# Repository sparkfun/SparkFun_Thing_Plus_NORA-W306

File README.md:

SparkFun Thing Plus - NORA-W306
========================================

[*SparkFun Thing Plus - NORA-W306 (WRL-21637)*](https://www.sparkfun.com/products/21637)

The SparkFun Thing Plus - NORA-W306 is a Feather form-factor development board equipped with the u-blox NORA-W306 module. The module contains a Realtek RTL8720DF, which has an integrated single-chip low-power dual-band (2.4GHz and 5GHz) Wireless LAN (WLAN) and Bluetooth&reg; Low Energy (BLE 5.3) communication microcontroller. It also consists of a dual processor core: Arm Cortex-M33 and Cortex-M23. To complement the module's low-power options, we've optimized components and added the ability to depower all subsystems to conserve as much power as possible for remote battery-powered applications.

Repository Contents
-------------------

* **.github/workflows** - YAML files used for GitHub Actions and GitHub Pages/mkdocs
* **/Hardware** - Eagle design files (.brd, .sch)
  * **/Production** - Production panel files (.brd)
* **/docs** - Online documentation files
  * **/assets** - Folder containing all the file assets used for product documentation
    * **/board_files** - Copy of design files used for product documentation
    * **/component_documentation** - Datasheets and manuals for hardware components
    * **/img** - Images for product documentation
  * **/github** - Files stating how to contribute and filing issues used for product documentation
  * **/javascript** - Folder containing custom javascript used for product documentation
  * **/stylesheet** - Folder containing CSS files used for product documentation
* **/overrides** - Customization files used for product documentation
  * **/.icons** - Icons used for GitHub used for product documentation
  * **./partials** - Used for product documentation

Documentation
--------------

* **[Installing an Arduino Library Guide](https://learn.sparkfun.com/tutorials/installing-an-arduino-library)** - Basic information on how to install an Arduino library.
* **Arduino Libraries**
    * **[MAX17048 LiPo Fuel Gauge](https://github.com/sparkfun/SparkFun_MAX1704x_Fuel_Gauge_Arduino_Library)**
    * **[SdFat](https://github.com/greiman/SdFat)**
    * **[Qwiic OLED Display](https://github.com/sparkfun/SparkFun_Qwiic_OLED_Arduino_Library)**
* **[Graphical Datasheet](https://github.com/sparkfun/Graphical_Datasheets/blob/main/Datasheets/NORA-W306/SparkFun_Thing_Plus_NORA-W306_u-blox.pdf)**
* **[Fritzing Part](https://github.com/sparkfun/Fritzing_Parts/blob/main/products/21637_sfe_thing_plus_u-blox_NORA-W306_development_board_lipo_charger_fuel_gauge_qwiic_WS2812.fzpz)**
* **[Realtek: Arduino Board Support Files](https://github.com/ambiot/ambd_arduino)**
* **[Hookup Guide](https://docs.sparkfun.com/SparkFun_Thing_Plus_NORA-W306)** - Basic hookup guide for the SparkFun Thing Plus NORA-W306.

Product Versions
----------------

* [WRL-21637](https://www.sparkfun.com/products/21637) - v1.0

Version History
---------------
* v1.0 - Initial Release

License Information
-------------------

This product is _**open source**_!

Please review the LICENSE.md file for license information.

If you have any questions or concerns on licensing, please contact technical support on our [SparkFun forums](https://forum.sparkfun.com/viewforum.php?f=152).

Distributed as-is; no warranty is given.

- Your friends at SparkFun.

_<COLLABORATION CREDIT>_

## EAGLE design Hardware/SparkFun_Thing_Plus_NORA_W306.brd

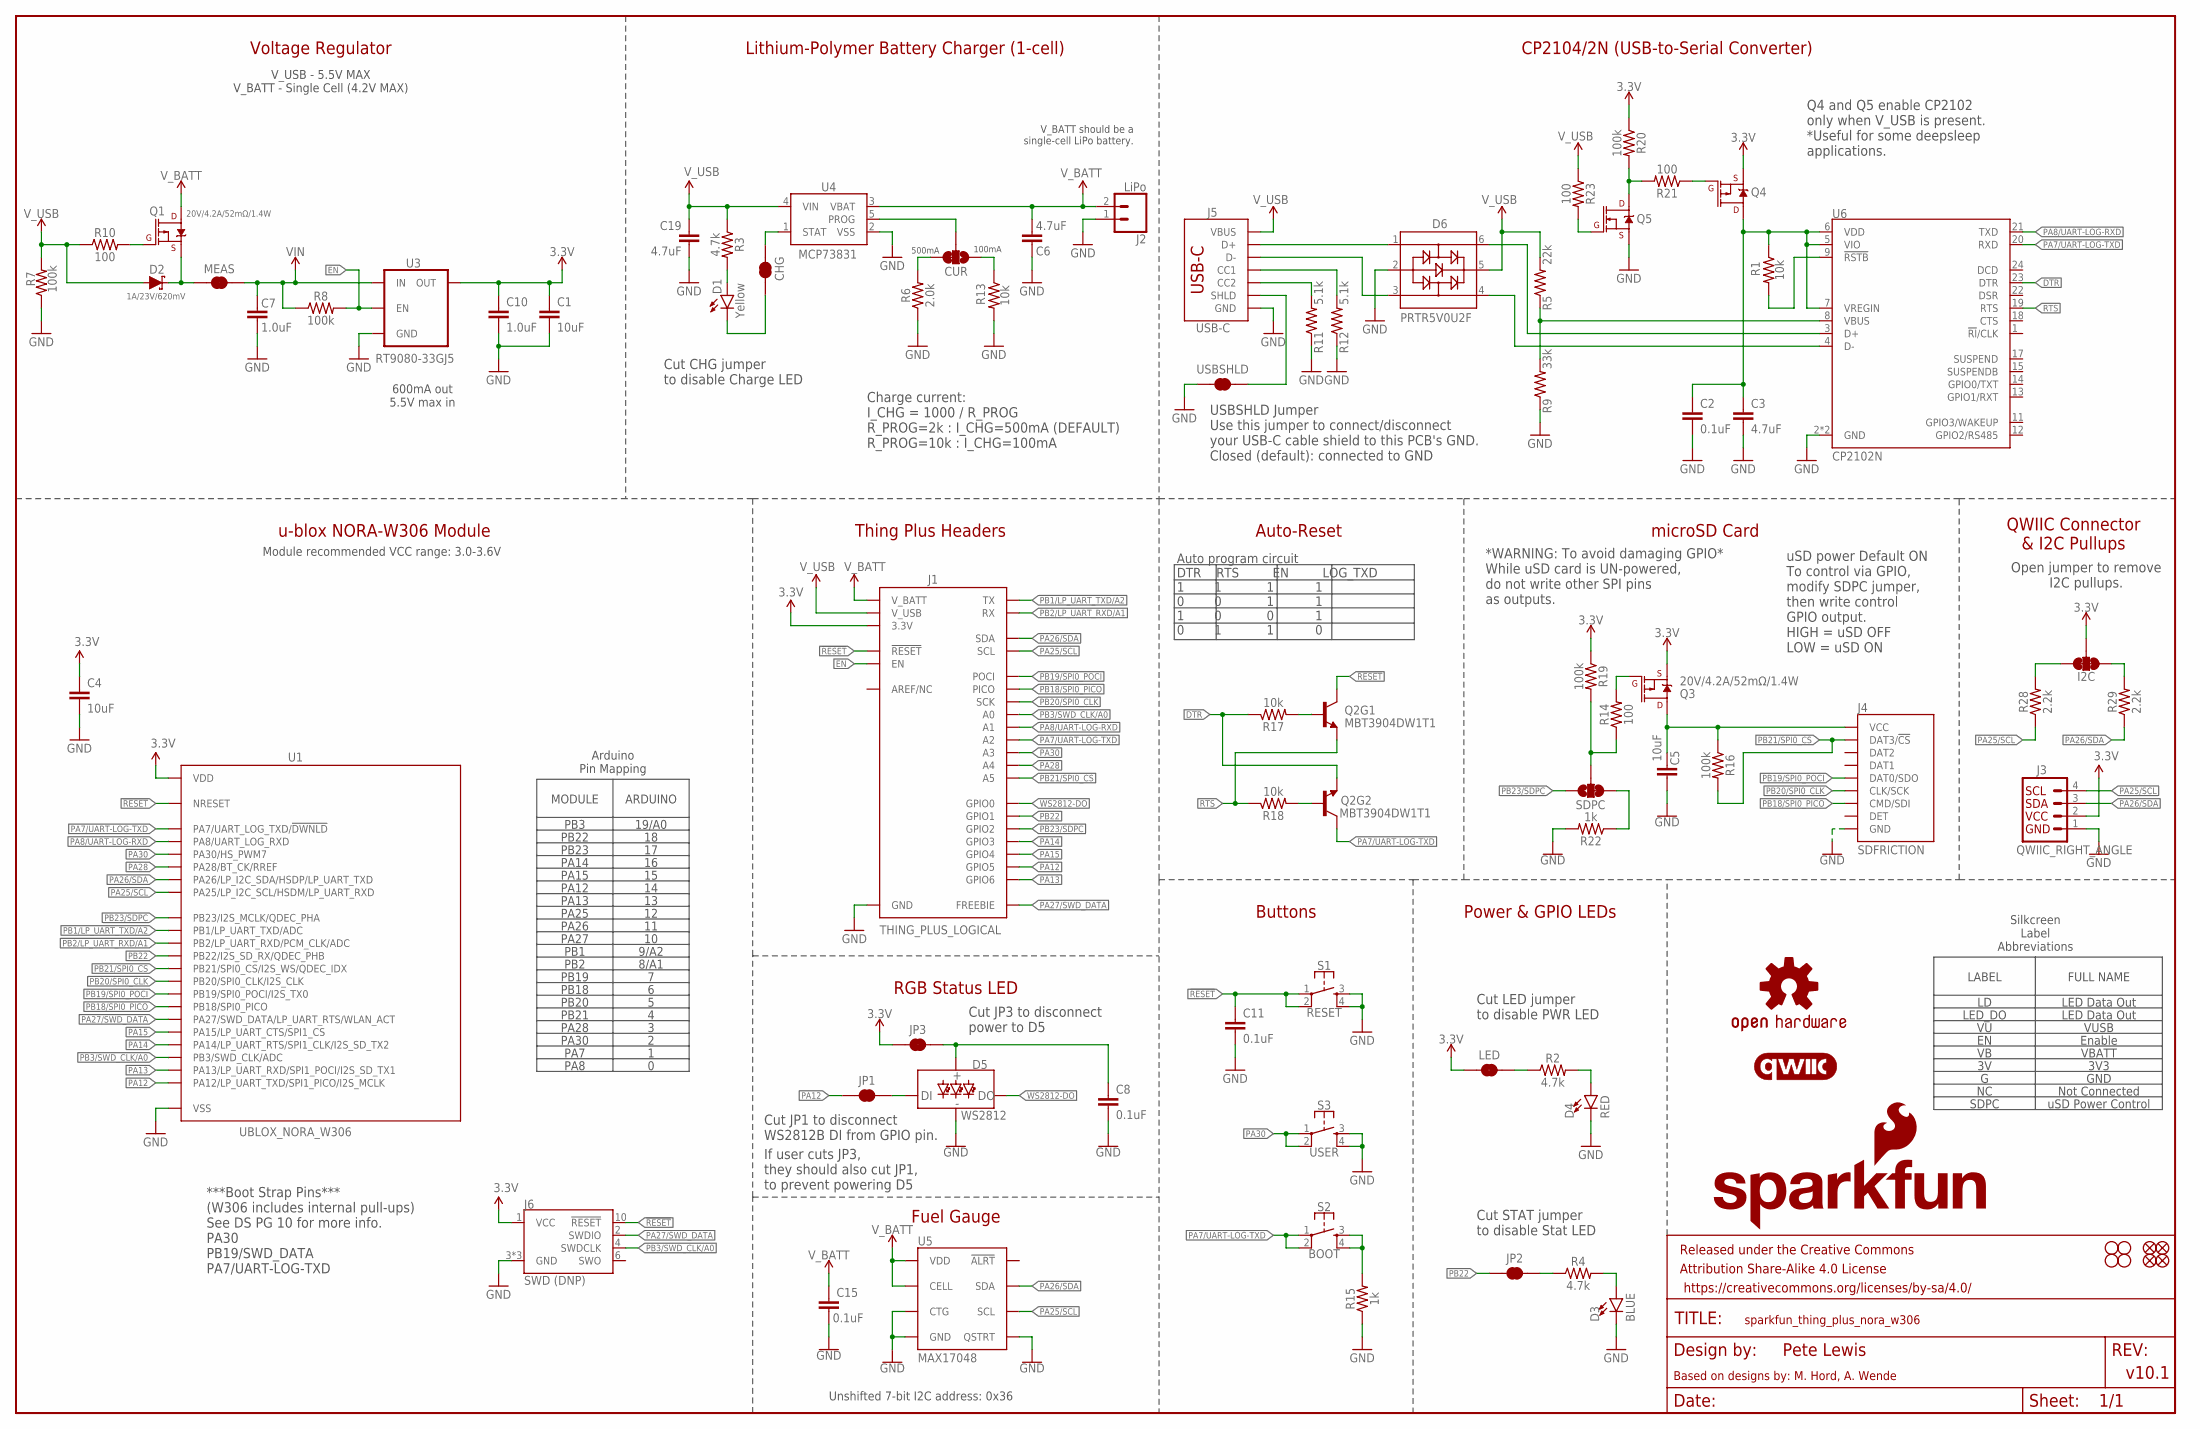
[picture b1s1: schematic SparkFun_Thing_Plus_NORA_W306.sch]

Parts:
C1, C4, C5: 10uF; 0402-TIGHT
C2, C8, C11, C15: 0.1uF; 0402-TIGHT
C3, C6, C19: 4.7uF; 0603
C7, C10: 1.0uF; 0402-TIGHT
CHG: JUMPER-SMT_2_NC_TRACE_SILK; SMT-JUMPER_2_NC_TRACE_SILK
CUR: JUMPER-SMT_3_1-NC_TRACE_SILK; SMT-JUMPER_3_1-NC_TRACE_SILK
D1: Yellow; LED-0603
D2: 1A/23V/620mV; SOD-323
D3: BLUE; LED-0603
D4: RED; LED-0603
D5: WS2812; WS2812-2020
D6: PRTR5V0U2F; SOT886
FD1, FD2, FD3, FD4: FIDUCIALUFIDUCIAL; FIDUCIAL-MICRO
FRAME1: FRAME-LEDGER; CREATIVE_COMMONS
H1, H2, H3, H4: STAND-OFF
I2C: JUMPER-SMT_3_2-NC_TRACE_SILK; SMT-JUMPER_3_2-NC_TRACE_SILK
J1: THING_PLUS_LOGICAL; THING_PLUS
J2: LiPo; JST-2-SMD
J3: QWIIC_RIGHT_ANGLE; JST04_1MM_RA
J4: SDFRICTION; MICROSD_TINY
J5: USB-C; USB-C-16P-4LAYER-ISOLATED
J6: SWD (DNP); 2X5-SMD-UNSHROUDED_DNP_NO_PASTE
JP1, JP2, JP3: JUMPER-SMT_2_NC_TRACE_SILK; SMT-JUMPER_2_NC_TRACE_SILK
LED: JUMPER-SMT_2_NC_TRACE_SILK; SMT-JUMPER_2_NC_TRACE_SILK
LOGO2: OSHW-LOGOM; OSHW-LOGO-M
LOGO3: SFE_LOGO_NAME_FLAME.1_INCH; SFE_LOGO_NAME_FLAME_.1
LOGO6: QWIIC_LOGO_4MM; QWIIC_4MM
MEAS: JUMPER-COMBO_2_NC_TRACE; COMBO-JUMPER_2_NC_TRACE
Q1, Q3, Q4: 20V/4.2A/52mΩ/1.4W; SOT23-3
Q2: MBT3904DW1T1; SC70-6
Q5: 20V/0.2A/8MHz/1.2Ω/1Vth; SOT-416FL
R1, R13, R17, R18: 10k; 0402-TIGHT
R2, R3, R4: 4.7k; 0402-TIGHT
R5: 22k; 0402-TIGHT
R6: 2.0k; 0603
R7, R8, R16, R19, R20: 100k; 0402-TIGHT
R9: 33k; 0402-TIGHT
R10, R14, R21, R23: 100; 0402-TIGHT
R11, R12: 5.1k; 0402-TIGHT
R15, R22: 1k; 0402-TIGHT
R28, R29: 2.2k; 0402-TIGHT
S1: RESET; TACTILE_SWITCH_SMD_4.6X2.8MM
S2: BOOT; TACTILE_SWITCH_SMD_4.6X2.8MM
S3: USER; TACTILE_SWITCH_SMD_4.6X2.8MM
SDPC: JUMPER-SMT_3_1-NC_TRACE_SILK; SMT-JUMPER_3_1-NC_TRACE_SILK
U1: UBLOX_NORA_W306; UBLOX-NORA-W3
U3: RT9080-33GJ5; SOT23-5
U4: MCP73831; SOT23-5
U5: MAX17048; DFN-8
U6: CP2102N; QFN24
USBSHLD: JUMPER-SMT_2_NC_TRACE_SILK; SMT-JUMPER_2_NC_TRACE_SILK

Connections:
3.3V: C1.1, C4.1, C10.1, I2C.2, J1.27 (3.3V), J3.2, J6.1 (VCC), JP3.1, LED.1, Q3.2 (S), Q4.2 (S), R19.1, R20.1, U1.A7 (VDD), U1.A8 (VDD), U1.B7 (VDD), U3.5 (OUT)
!RESET!: C11.1, J1.28 (!RESET), J6.10 (!RESET), Q2.3 (C), S1.1, S1.2, U1.J3 (NRESET)
CC1: J5.A5 (CC1), R12.2
CC2: J5.B5 (CC2), R11.2
CHG: CHG.2, U4.1 (STAT)
DTR: Q2.1 (E), R17.1, U6.23 (DTR)
EN: J1.11 (EN), R8.2, U3.3 (EN)
GND: C1.2, C2.2, C3.2, C4.2, C5.2, C6.2, C7.2, C8.2, C10.2, C11.2, C15.2, C19.2, D3.C, D4.C, D5.GND, D6.2, J1.25 (GND), J2.1 (2), J3.1, J4.6 (GND), J4.GND1 (GND), J4.GND2 (GND), J4.GND3 (GND), J4.GND4 (GND), J4.GND5 (GND), J4.GND6 (GND), J5.GND, J5.GND2 (GND), J6.3 (GND), J6.5 (GND), J6.9 (GND), Q5.2 (S), R6.1, R7.1, R9.1, R11.1, R12.1, R13.2, R15.1, R22.2, S1.3, S1.4, S3.3, S3.4, U1.A1 (VSS), U1.A9 (VSS), U1.B2 (VSS), U1.B8 (VSS), U1.E4 (VSS), U1.E5 (VSS), U1.F4 (VSS), U1.F5 (VSS), U1.K2 (VSS), U1.K3 (VSS), U1.K5 (VSS), U1.K7 (VSS), U1.K8 (VSS), U1.L1 (VSS), U1.L9 (VSS), U1.M1 (VSS), U1.M2 (VSS), U1.M8 (VSS), U1.M9 (VSS), U3.2 (GND), U4.2 (VSS), U5.1 (CTG), U5.4 (GND), U5.6 (QSTRT), U5.9 (GND), U6.2 (GND), U6.PAD (GND), USBSHLD.1
unnamed: R1.2, U6.9 (!RSTB)
unnamed: D3.A, R4.2
unnamed: Q2.5 (B), R17.2
unnamed: R5.1, R9.2, U6.8 (VBUS)
unnamed: Q2.2 (B), R18.2
unnamed: CHG.1, D1.C
unnamed: Q1.1 (G), R10.2
unnamed: R15.2, S2.3, S2.4
unnamed: CUR.2, U4.5 (PROG)
unnamed: D5.DI, JP1.2
unnamed: CUR.1, R13.1
unnamed: LED.2, R2.1
unnamed: CUR.3, R6.2
unnamed: D4.A, R2.2
unnamed: D6.6, U6.3 (D+)
unnamed: D6.1, J5.A6 (D+), J5.B6 (D+)
unnamed: D1.A, R3.2
unnamed: D6.4, U6.4 (D-)
unnamed: D6.3, J5.A7 (D-), J5.B7 (D-)
unnamed: I2C.3, R28.2
unnamed: I2C.1, R29.2
unnamed: JP2.2, R4.1
unnamed: D2.C, MEAS.1, MEAS.3 (1), Q1.2 (S)
unnamed: Q3.1 (G), R14.2
unnamed: C5.1, J4.4 (VCC), Q3.3 (D), R16.1
unnamed: R14.1, R19.2, SDPC.2
unnamed: Q5.3 (D), R20.2, R21.2
unnamed: C8.1, D5.VCC, JP3.2
unnamed: C2.1, C3.1, Q4.3 (D), R1.1, U6.5 (VIO), U6.6 (VDD), U6.7 (VREGIN)
unnamed: Q4.1 (G), R21.1
unnamed: Q5.1 (G), R23.2
unnamed: R22.1, SDPC.3
PA7/UART-LOG-TXD: J1.22 (A2), Q2.6 (C), S2.1, S2.2, U1.A5 (PA7/UART_LOG_TXD/!DWNLD!), U6.20 (RXD)
PA8/UART-LOG-RXD: J1.23 (A1), U1.A6 (PA8/UART_LOG_RXD), U6.21 (TXD)
PA12: J1.4 (GPIO5), JP1.1, U1.J9 (PA12/LP_UART_TXD/SPI1_PICO/I2S_MCLK)
PA13: J1.3 (GPIO6), U1.J8 (PA13/LP_UART_RXD/SPI1_POCI/I2S_SD_TX1)
PA14: J1.6 (GPIO3), U1.H9 (PA14/LP_UART_RTS/SPI1_CLK/I2S_SD_TX2)
PA15: J1.5 (GPIO4), U1.H8 (PA15/LP_UART_CTS/SPI1_CS)
PA25/SCL: J1.2 (SCL), J3.4, R28.1, U1.C2 (PA25/LP_I2C_SCL/HSDM/LP_UART_RXD), U5.7 (SCL)
PA26/SDA: J1.1 (SDA), J3.3, R29.1, U1.C1 (PA26/LP_I2C_SDA/HSDP/LP_UART_TXD), U5.8 (SDA)
PA27/SWD_DATA: J1.13 (FREEBIE), J6.2 (SWDIO), U1.H2 (PA27/SWD_DATA/LP_UART_RTS/WLAN_ACT)
PA28: J1.20 (A4), U1.B3 (PA28/BT_CK/RREF)
PA30: J1.21 (A3), S3.1, S3.2, U1.B1 (PA30/HS_PWM7)
PB1/LP_UART_TXD/A2: J1.14 (TX), U1.D8 (PB1/LP_UART_TXD/ADC)
PB2/LP_UART_RXD/A1: J1.15 (RX), U1.E8 (PB2/LP_UART_RXD/PCM_CLK/ADC)
PB3/SWD_CLK/A0: J1.24 (A0), J6.4 (SWDCLK), U1.J2 (PB3/SWD_CLK/ADC)
PB18/SPI0_PICO: J1.17 (PICO), J4.3 (CMD/SDI), U1.G9 (PB18/SPI0_PICO)
PB19/SPI0_POCI: J1.16 (POCI), J4.7 (DAT0/SDO), U1.G8 (PB19/SPI0_POCI/I2S_TX0)
PB20/SPI0_CLK: J1.18 (SCK), J4.5 (CLK/SCK), U1.F9 (PB20/SPI0_CLK/I2S_CLK)
PB21/SPI0_CS: J1.19 (A5), J4.2 (DAT3/!CS!), R16.2, U1.F8 (PB21/SPI0_CS/I2S_WS/QDEC_IDX)
PB22: J1.8 (GPIO1), JP2.1, U1.E9 (PB22/I2S_SD_RX/QDEC_PHB)
PB23/SDPC: J1.7 (GPIO2), SDPC.1, U1.C8 (PB23/I2S_MCLK/QDEC_PHA)
RTS: Q2.4 (E), R18.1, U6.19 (RTS)
USB_SHLD: J5.SHLD1 (SHLD), J5.SHLD2 (SHLD), J5.SHLD3 (SHLD), J5.SHLD4 (SHLD), J5.SHLD5 (SHLD), J5.SHLD6 (SHLD), J5.SHLD7 (SHLD), J5.SHLD8 (SHLD), USBSHLD.2
VIN: C7.1, MEAS.2, MEAS.4 (2), R8.1, U3.1 (IN)
V_BATT: C6.1, C15.1, J1.12 (V_BATT), J2.2 (1), Q1.3 (D), U4.3 (VBAT), U5.2 (CELL), U5.3 (VDD)
V_USB: C19.1, D2.A, D6.5, J1.10 (V_USB), J5.VBUS1 (VBUS), J5.VBUS2 (VBUS), R3.1, R5.2, R7.2, R10.1, R23.1, U4.4 (VIN)
WS2812-DO: D5.DO, J1.9 (GPIO0)

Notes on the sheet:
CP2104/2N (USB-to-Serial Converter)
V_BATT should be a single-cell LiPo battery.
Charge current: I_CHG = 1000 / R_PROG R_PROG=2k : I_CHG=500mA (DEFAULT) R_PROG=10k : I_CHG=100mA
Voltage Regulator
Lithium-Polymer Battery Charger (1-cell)
600mA out 5.5V max in
u-blox NORA-W306 Module
Thing Plus Headers
v10.1
QWIIC Connector & I2C Pullups
Pete Lewis
Power & GPIO LEDs
Based on designs by: M. Hord, A. Wende
V_USB - 5.5V MAX V_BATT - Single Cell (4.2V MAX)
100mA
500mA
Module recommended VCC range: 3.0-3.6V
Buttons
Auto program circuit DTR RTS EN LOG_TXD 1 1 1 1 0 0 1 1 1 0 0 1 0 1 1 0
Auto-Reset
USBSHLD Jumper Use this jumper to connect/disconnect your USB-C cable shield to this PCB's GND. Closed (default): connected to GND
Cut LED jumper to disable PWR LED
microSD Card
RGB Status LED
Fuel Gauge
Unshifted 7-bit I2C address: 0x36
Cut JP1 to disconnect WS2812B DI from GPIO pin.
***Boot Strap Pins*** (W306 includes internal pull-ups) See DS PG 10 for more info. PA30 PB19/SWD_DATA PA7/UART-LOG-TXD
Arduino Pin Mapping
9/A2
8/A1
19/A0
PA8
PA7
PA15
PA14
PA12
PA13
PA25
PA26

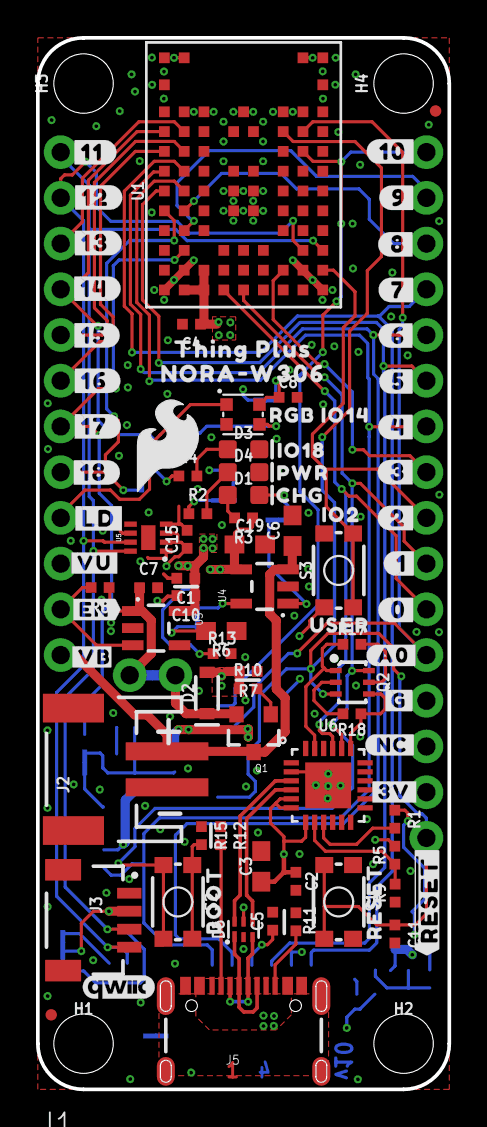
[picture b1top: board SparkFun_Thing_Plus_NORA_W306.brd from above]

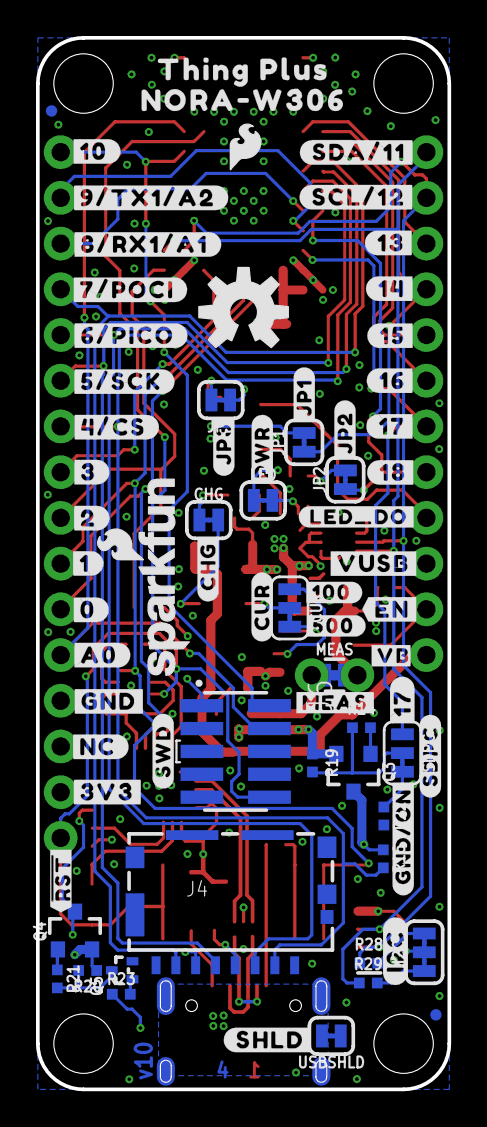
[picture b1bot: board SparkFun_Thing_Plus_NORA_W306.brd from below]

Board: 4 copper layers, 22.9 x 58.4 mm, 170 parts (74 on the bottom side), 66 nets.

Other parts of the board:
U$1, U$22: #17#11
U$2: BOOT0
U$3: #MEAS#1714141838
U$4: IO180
U$5: NORA#W3060
U$6: ##RST##23061714141845
U$7: USER0
U$8: SFE_LOGO_FLAME_.2
U$9: IO20
U$10: #GND#ON#3061714141842
U$11: #SDPC#0
U$12: #A0#1
U$13: #SDA#11#28
U$14: #17#28
U$15: #0#4
U$16: #1#4
U$17: #SCL#12#28
U$18: #18#28
U$19: SFE_LOGO_FLAME_.1
U$20: #LD#29
U$21: RGB_IO140
U$23: PWR0
U$24: #CUR#0
U$25: THING_PLUS1714141839
U$26, U$77: #VB26
U$28: NORA#W3061714141840
U$30: #13#13
U$31: #14#14
U$32: #15#15
U$33: #16#16
U$35: #18#18
U$36: #11#91420
U$37: #12#91420
U$38: #13#91420
U$39: #14#91420
U$40: #15#91420
U$41: #VUSB#0
U$42: #JP3#23061714141846
U$43: #EN#0
U$44: #16#91420
U$45: #3V3#0
U$46: #NC#2
U$47: #A0#18
U$48: #8#91421
U$49: #7#8
U$50: #6#8
U$51: #5#8
U$52: #4#8
U$53: #3#8
U$54: #2#8
U$55: #1#8
U$56: #0#8
U$57: #3V#23
U$58: #JP2#0
U$59: ORDERING_INSTRUCTIONS
U$60: #SWD#501
U$61: #100#23061714141846
U$62: THING_PLUS_0
U$63: #SHLD#9
U$64: #GND#10
U$65: #JP1#0
U$66: #PWR#14
U$67: #CHG#13
U$68: ##RESET##19
U$69: #NC#21
U$70: #9#10
U$71: #LED_DO#0
U$72: #I2C#3
U$73: #500#23061714141846
U$74: #10#11
U$75: #G#22
U$76: #VU#23
U$78: CHG0
U$79: RESET0
U$80: #EN#27
U$81: #2#28
U$82: #3#28
U$83: #4#CS#28
U$84: #5#SCK#28
U$85: #6#PICO#28
U$86: #7#POCI#28
U$87: #9#TX1#A2#28
U$88: #8#RX1#A1#28
U$91: #10#28

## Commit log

2023-01-10 device created in mini library
2023-01-13 Proto Layout almost done
    -needs buzzard labels
2023-01-16 Routed Log UART RX/TX to header pins
2023-01-17 Bottom silk done, top silk needs placement
2023-01-17 Switch to QFN28 package of CP2102
    -also finished top silk labels
2023-01-17 cp2102N_QFN28 Prod_ID
2023-01-18 checklist run eng pre review
    -added jumper to disconnect RGB LED
    -added prod_id for module
    -added board thickness to ordering instructions on tdocu
    -added name/value texts to module footprint
    -moved a lot of vias and traces to avoid silk overlap
2023-01-18 datasheets
2023-01-18 Switch IO controlling STAT LED from 13 to 16
    -to avoid having an LED on a strapping pin
2023-01-18 added note about boot strap pins in schematic
2023-01-18 arduino pin mapping table in schematic
2023-01-19 nudged r11, fixed sch table
    -added silk outline to module footprint
2023-01-19 nudged SDA trace for better btm gnd flow
2023-01-19 module fp pad spacing corrected
    -all vector text in schematic
    -removed units in some measures
2023-01-19 Design review changes
    -removed un-used net class "power"
    -renamed N_RESET net to !RESET!
    -added "USER" silk to button
    -flipped RESET buzzard label to match jumper label orientations
    -added chg jumper text paragraph to sch
    -nudged 3.3V vias/poly (connection from VREG to inner layer) to free up space from nearby passive.
2023-01-19 added debounce cap to reset
2023-01-19 extended tb restricts outward .1mm to match ds
2023-01-19 exteneded tb restrices out past module end like ds
    -this also highlighted that I should bring in the inner GND layer back as well, so did that too.
2023-01-20 Renamed and updated label to STAT Jumper to JP4
2023-01-30 Switched to SPI1 and alternate TX1/RX1 pins
2023-01-30 bumping version to v02
2023-01-30 BOM consolidation
    -added surface finish instructions (HASL)
    -removed layer 100
    -all 0.1uF caps are now the same 16V part (there used to be 3 different types).
    -all 10uF are now the same part (just changed one cap from 0603 to 0402, but had the same voltage rating).
    -all 4.7uF are now 0603, 35V, to accommodate VBATT inputs.
2023-01-31 Added SWD header to bottom side
2023-01-31 nudged trace for better gnd flow
    added gnd via near swd layer transfer
2023-01-31 SWD header to DNP and bumped version to v03
2023-02-01 v03 proto panel and gerbers
2023-03-06 removed paste from cortex debug SMD footprint (DNP)
    -also bumped version to v04
2023-03-10 Correcting SWD_DATA and SWD_CLK
    -In the Symbol Pin names, Removed SWD DATA and CL from PB18/PB19
    -Removed PDM mic
2023-03-10 SPI0_POCI pin name in Symbol
2023-03-13 Switched CP2102 to QFN24 package type
2023-03-20 Rerouted with new pin selections
    -SPI0 now used for "main" SPI headers and uSD
    -SPI1 PICO pin used for WS2812 control
    -RX1/TX1 pins changed to other option on module
    -I2C pins changed to other option on module
    -SWD lines routed to DNP header on bottom side.
    -most GPIOs switched/rerouted *note, Arduino pin map table not yet updated*
2023-03-20 Silk Labels updated
    -and some minor layout tweaks
2023-03-21 Corrected User button and STAT LED silk
    -Moved button to Arduino "17"
2023-03-21 rerouting some stuff
    -Re-routed SPI lined to removed one via in SPI0_CLK net
    -Nudged some stuff to create a bit more clearance between RX/TX log and SPI traces on long north-south journey.
2023-03-22 Updated Arduino pin mapping table in SCH
2023-03-22 Added V-MEAS jumper
2023-03-22 Moved SDA/SCL from inner to bottom layer
2023-03-22 Removed V_BUS plane on inner layer
    To avoid splitting up the 3.3V plane on the inner layer, I decided to route V_USB (instead of using an additional separate plane).
    Added some stitching traces/polys to stich up the 3.3V plane.
2023-03-23 Updated to new 0603 RED LED
    -also updated the limiting resistor to correct value (4.7K) for DIO-17976
2023-03-24 Pre-group Review of v04 Changes
    -moved logos to right box in SCH
    -added column names to may pin mapping table in SCH
    -adjusted SCH note about boot strapping pin internal pullups
    -"single-cell" lipo batt note moved to single line
    -changed current jumper silk to be "CUR"
    -changed MEAS to smaller size and flat ends to fit better
2023-03-24 more tweaks pre-review
    -added another ground via near I2C lines NW corner
    -Added GND trace to connect GND near user button
    -fixed some airwires caused by the new trestrict rectangles. Just routed the "missing" GND connections.
2023-03-24 Added tKeepout around module footprint
2023-03-24 Label Abbreviations table in SCH
2023-03-28 WIP adding switches to uSD and CP2102
2023-03-29 layout work done for switches for uSD & cp2102
2023-03-29 added jumper to cut power to WS2812B
2023-03-29 corrected JP1 comment text
2023-03-29 replaced SDPC jumper using correct library
2023-03-29 updating visible layers when you open it
2023-03-29 final review before ordering proto changes
    -added 100 ohm slow down resistor to CP2102 mosfet control gate pin
    -added 1K pull down off of SCPC jumper to protect gpio in case user accidentally closes all 3 pads on jumper.
    -changed VBATT trace on inner layer so it crosses SDA/SCL at 90
    -added gnd via above user botton
    -added full size SFE logo to bottom silk
    -center product name silk
2023-03-29 added gate resistor to Q5
2023-03-29 adjusted uSD gpio warning in SCH
2023-03-29 proto panel v04
2023-03-29 protopanel v04 brd file save
2023-04-04 Via size decreased to reach 5 mil clearances
    -decreased via size to provide more clearance from pads under the module
    -also decrease GND traces under the module to 16 mil.
    -also adjusted USB D+/D- for closer to 90 ohms impeadance (8mil trace width and 6mil gap between them).
    -bumped version to v05 to keep file names straight with collaborators on this project
2023-04-04 proto panel v05
2023-05-11 vreg datasheets
    -xc622 is the current plan, but may use the DS9080-07 if it tests out okay.
2023-05-11 Bumped version to v10
2023-05-15 Tweaks from final mini group review.
    -corrected "back powering" to "powering" on sch note about JP1
    -Swapped R7 from 10K to 100K for better power savings if powered from USB or 5V battery
    -nudging for better GND flow
    -peppered in some more gnd vias
    -adjusted v_batt trace and via from header to fuel gage for better gnd flow
    -adjusted SWD Traces for a little more spacing in between them
2023-05-15 one more via
    -one more via in between pads 14 and 15. Had a long ground peninsula with no gnd at the end.
    -nudged PB1 trace away a tiny bit to allow ground flow.
2023-05-18 Production panel and gerbers v10
2023-08-30 Started adapting NINA tb clone to NORA
2024-06-03 removing old prototype panel gerbers
2024-06-03 renaming production gerbers file to v10 for ordering clarity
2024-06-10 Update Related Docs
2024-07-10 Initial Push GitHub Pages
2024-07-13 Link Additional Component Datasheets and Arduino Library
2024-07-14 Add Photos and Additional Sections for Basic Hookup Guide
2024-07-16 Update Tutorial
    - Link Graphical Datasheet
    - Link SdFat Arduino Library
2024-07-16 Update Graphical Datasheet, Add Fritzing Part
2024-07-16 Add MicroSD Card Test Example
2024-07-17 Add Connection Table, Fritzing Diagram for Demo
2024-07-17 Break up Arduino Examples into Separate Pages
2024-07-17 Add Example 6 with a microSD card
2024-07-17 SparkFun_ThingPlus_NORAW306_SdCard.ino
2024-07-17 DeepSleepBlink example
2024-07-17 DeepSleepTempLogger WIP
    -got it sleeping and printing data to terminal.
2024-07-18 Link Tutorial, Update Image so more of a "landscape," adjust CSS to limit code height and add vertical scrolling
2024-07-18 Add Deep Sleep Blink Example
2024-07-18 DeepSleepTempLogger working
2024-07-18 Update Materials, Minor Update to Content in Tutorial
2024-07-19 Make space for an additional example
2024-07-25 Add Deep Sleep DataLogging Arduino Example to Tutorial
2024-08-01 Link Product Showcase Video
2024-08-01 Deployed 91c20f9 with MkDocs version: 1.6.0
2024-09-13 Add demo video for low power mode
2024-09-13 Deployed df15383 with MkDocs version: 1.6.1
2024-10-28 Add cookies
2024-10-29 Deployed f30f6ad with MkDocs version: 1.6.1
2025-02-04 swapped VREG (U3) for RT9080-33
    -swapped vreg (u3) for rt9080-33
    -updated schematic notes to reflect new max input (5.5V)
    -updated sch version to v10.1
2026-06-03 Deployed 24c70e9 with MkDocs version: 1.6.1

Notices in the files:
Example_Code/SparkFun_ThingPlus_NORAW306_DeepSleepBlink/SparkFun_ThingPlus_NORAW306_DeepSleepBlink.ino:
MIT License
Copyright (c) 2024 SparkFun Electronics
parts and their libraries:
SparkFun-Resistors: Licensing: Creative Commons ShareAlike 4.0 International - https://creativecommons.org/licenses/by-sa/4.0
SparkFun-Aesthetics: Released under the Creative Commons Attribution Share-Alike 4.0 License
SparkFun-Aesthetics: https://creativecommons.org/licenses/by-sa/4.0
